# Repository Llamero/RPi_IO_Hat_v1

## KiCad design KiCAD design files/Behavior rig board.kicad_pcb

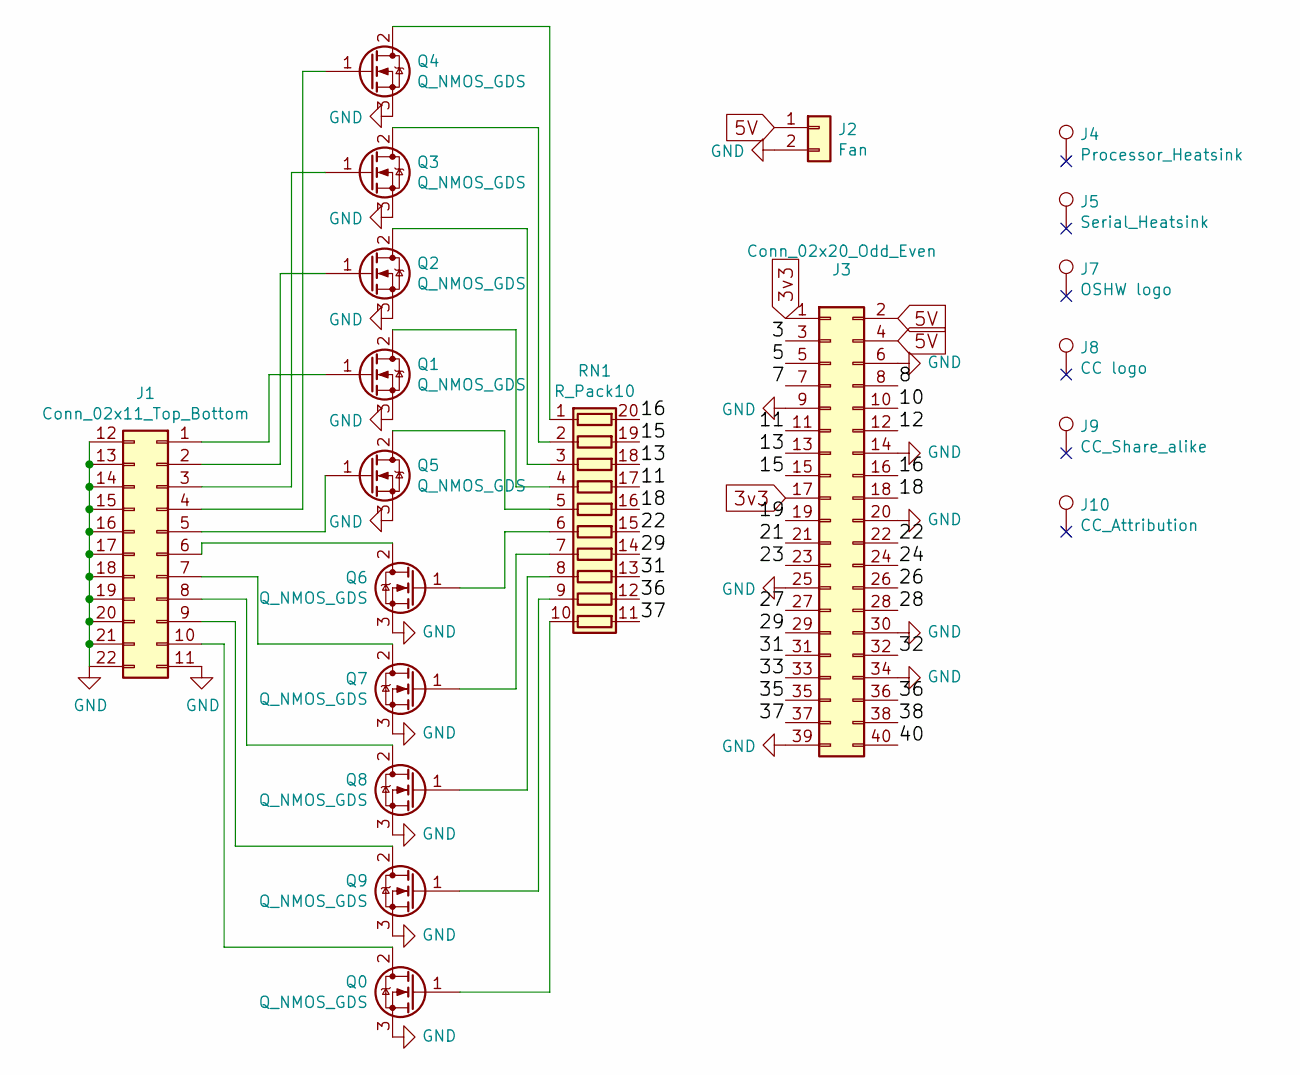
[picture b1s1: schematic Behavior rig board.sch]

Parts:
J1: Conn_02x11_Top_Bottom; PHOENIX_1848736-11x2_terminal_block; Digikey Part # 277-12233-ND
J2: Fan; SolderWirePad_2x_1-5mmDrill; Digikey Part # 259-1561-ND
J3: Conn_02x20_Odd_Even; Pi_Stackable_Socket_Straight_2x20_Pitch2.54mm; Digikey Part # SAM11959-ND
J4: Processor_Heatsink; WV_19x19mm_heatsink; Digikey Part # 345-1149-ND
J5: Serial_Heatsink; Digikey Part # AE11388-ND
J7: OSHW logo; OSHW-Symbol_6.7x6mm_SilkScreen
J8: CC logo; CC_silkscreen
J9: CC_Share_alike
J10: CC_Attribution
Q0, Q1, Q2, Q3, Q4, Q5, Q6, Q7, Q8, Q9: Q_NMOS_GDS; SOT-89-3; Digikey Part # ZVN4525ZCT-ND
RN1: R_Pack10; Bourns_4820P-1-102LF; Digikey Part # 4820P-1-102LFCT-ND

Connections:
3v3: J3.1, J3.17
5V: J2.1, J3.2, J3.4
/3: J3.3
/5: J3.5
/7: J3.7
/8: J3.8
/10: J3.10
/11: J3.11, RN1.17 (R4.2)
/12: J3.12
/13: J3.13, RN1.18 (R3.2)
/15: J3.15, RN1.19 (R2.2)
/16: J3.16, RN1.20 (R1.2)
/18: J3.18, RN1.16 (R5.2)
/19: J3.19
/21: J3.21
/22: J3.22, RN1.15 (R6.2)
/23: J3.23
/24: J3.24
/26: J3.26
/27: J3.27
/28: J3.28
/29: J3.29, RN1.14 (R7.2)
/31: J3.31, RN1.13 (R8.2)
/32: J3.32
/33: J3.33
/35: J3.35
/36: J3.36, RN1.12 (R9.2)
/37: J3.37, RN1.11 (R10.2)
/38: J3.38
/40: J3.40
GND: J1.11, J1.12, J1.13, J1.14, J1.15, J1.16, J1.17, J1.18, J1.19, J1.20, J1.21, J1.22, J2.2, J3.6, J3.9, J3.14, J3.20, J3.25, J3.30, J3.34, J3.39, Q0.3 (S), Q1.3 (S), Q2.3 (S), Q3.3 (S), Q4.3 (S), Q5.3 (S), Q6.3 (S), Q7.3 (S), Q8.3 (S), Q9.3 (S)
unnamed: J1.1, Q1.1 (G)
unnamed: J1.2, Q2.1 (G)
unnamed: J1.3, Q3.1 (G)
unnamed: J1.4, Q4.1 (G)
unnamed: J1.5, Q5.1 (G)
unnamed: J1.6, Q6.2 (D)
unnamed: J1.7, Q7.2 (D)
unnamed: J1.8, Q8.2 (D)
unnamed: J1.9, Q9.2 (D)
unnamed: J1.10, Q0.2 (D)
unnamed: Q0.1 (G), RN1.10 (R10.1)
unnamed: Q1.2 (D), RN1.4 (R4.1)
unnamed: Q2.2 (D), RN1.3 (R3.1)
unnamed: Q3.2 (D), RN1.2 (R2.1)
unnamed: Q4.2 (D), RN1.1 (R1.1)
unnamed: Q5.2 (D), RN1.5 (R5.1)
unnamed: Q6.1 (G), RN1.6 (R6.1)
unnamed: Q7.1 (G), RN1.7 (R7.1)
unnamed: Q8.1 (G), RN1.8 (R8.1)
unnamed: Q9.1 (G), RN1.9 (R9.1)

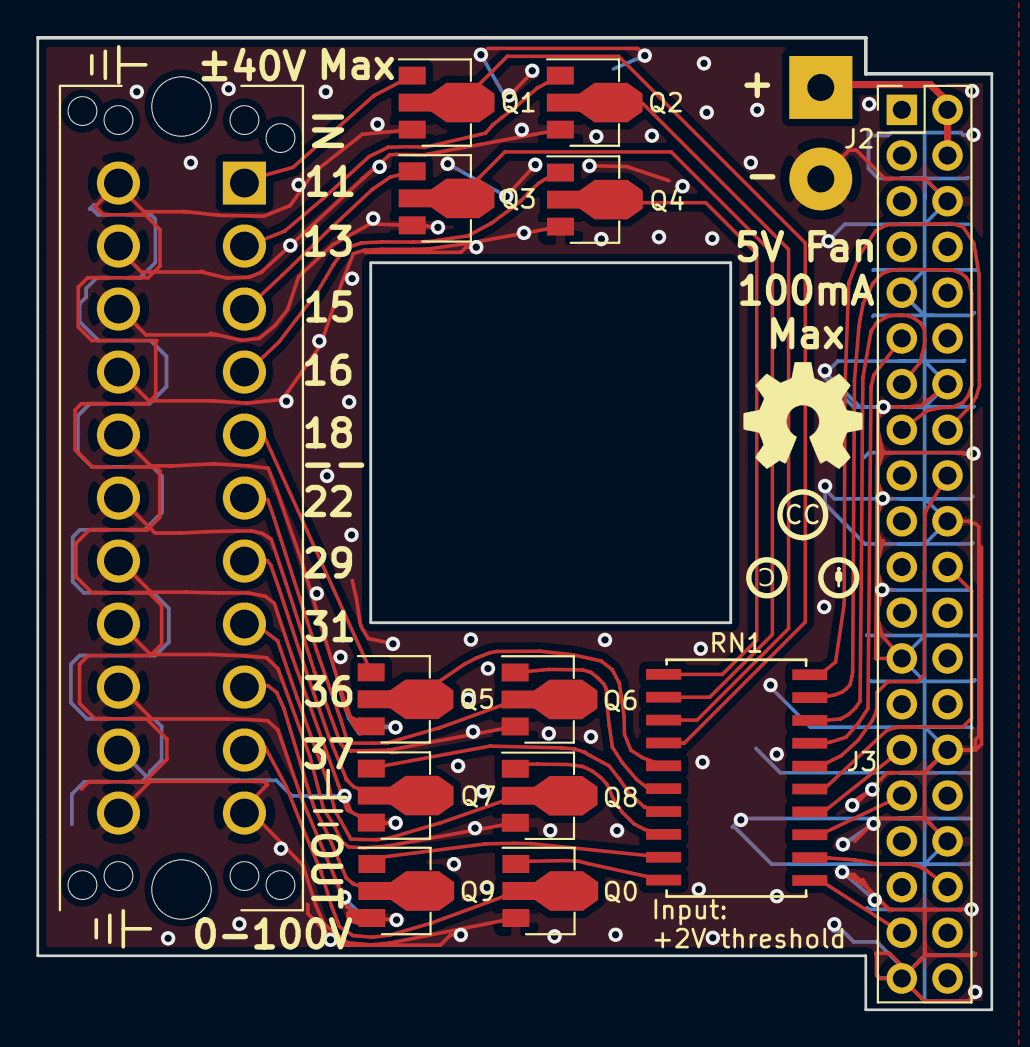
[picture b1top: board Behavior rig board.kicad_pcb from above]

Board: 2 copper layers, 53.0 x 54.0 mm, 19 parts (0 on the bottom side), 33 nets.

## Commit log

2019-02-22 Upload KiCAD files
2019-02-22 Creative Commons Attribution-ShareAlike 3.0
2019-02-23 Add gerber and CAD files
2019-02-23 BOM added
2019-02-23 Manual and BOM added
